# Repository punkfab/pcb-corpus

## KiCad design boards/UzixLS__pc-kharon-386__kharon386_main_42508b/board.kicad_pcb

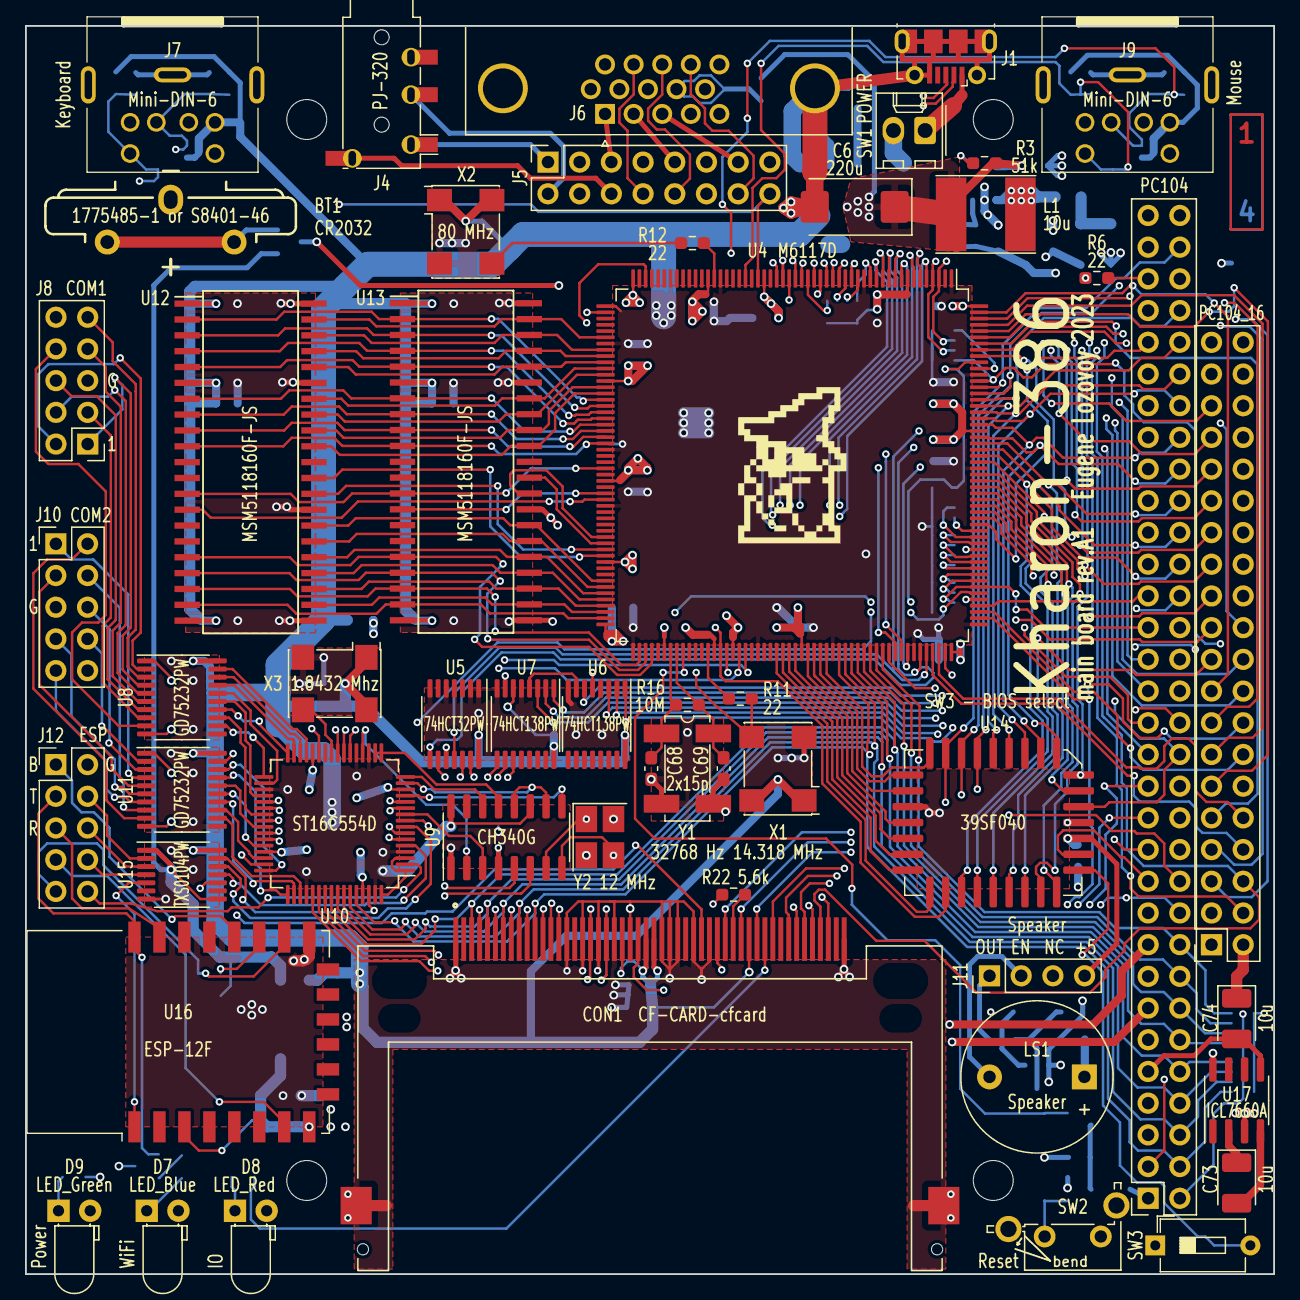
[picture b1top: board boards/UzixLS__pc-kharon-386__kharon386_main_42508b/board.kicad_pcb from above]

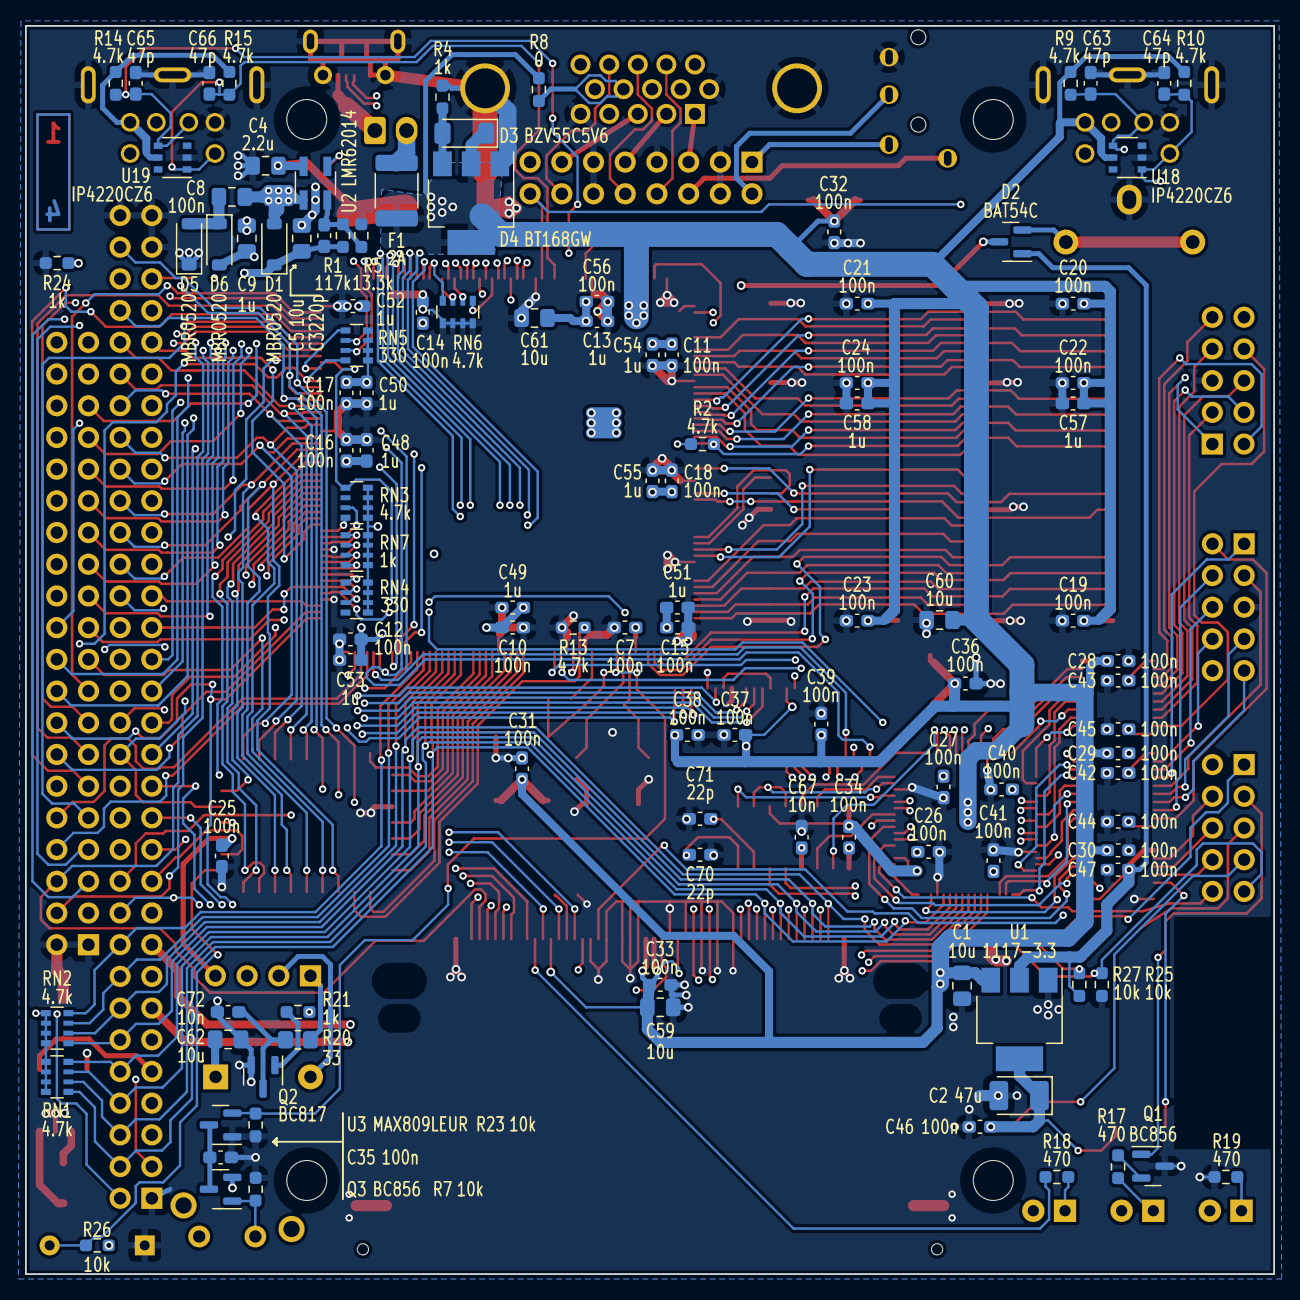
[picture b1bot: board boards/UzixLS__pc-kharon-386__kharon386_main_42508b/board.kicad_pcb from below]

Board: 4 copper layers, 100.0 x 100.0 mm, 169 parts (112 on the bottom side), 252 nets.

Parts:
BT1: 1775485-1 or S8401-46; CR2032V
C1, C5, C59, C60, C61, C62: 10u; C_0805_2012Metric_Pad1.18x1.45mm_HandSolder
C2: 47u; CP_EIA-3528-21_Kemet-B_Pad1.50x2.35mm_HandSolder
C3: 220p; C_0603_1608Metric_Pad1.08x0.95mm_HandSolder
C4: 2.2u; C_0805_2012Metric_Pad1.18x1.45mm_HandSolder
C6: 220u; CP_EIA-7343-31_Kemet-D_Pad2.25x2.55mm_HandSolder
C7, C10, C11, C12, C13, C14, C15, C16, C17, C18, C19, C20, C21, C22, C23, C24, C25, C26, C27, C28, C29, C30, C31, C32, C33, C34, C35, C36, C37, C38, C39, C40, C41, C42, C43, C44, C45, C46, C47: 100n; C_0603_1608Metric_Pad1.08x0.95mm_HandSolder
C8: 100n; C_0805_2012Metric_Pad1.18x1.45mm_HandSolder
C9: 1u; C_0805_2012Metric_Pad1.18x1.45mm_HandSolder
C48, C49, C50, C51, C52, C53, C54, C55, C56, C57, C58: 1u; C_0603_1608Metric_Pad1.08x0.95mm_HandSolder
C63, C64, C65, C66: 47p; C_0603_1608Metric_Pad1.08x0.95mm_HandSolder
C67, C72: 10n; C_0603_1608Metric_Pad1.08x0.95mm_HandSolder
C68, C69: 15p; C_0603_1608Metric_Pad1.08x0.95mm_HandSolder
C70, C71: 22p; C_0603_1608Metric_Pad1.08x0.95mm_HandSolder
C73, C74: 10u; CP_EIA-3528-21_Kemet-B_Pad1.50x2.35mm_HandSolder
CON1: CF-CARD-cfcard; TE_1734451-1-LONG
D1, D5, D6: MBR0520; D_SOD-123
D2: BAT54C; SOT-23
D3: BZV55C5V6; D_MiniMELF
D4: BT168GW; SOT-223-3_TabPin2
D7: LED_Blue; LED_D3.0mm_Horizontal_O1.27mm_Z6.0mm
D8: LED_Red; LED_D3.0mm_Horizontal_O1.27mm_Z6.0mm
D9: LED_Green; LED_D3.0mm_Horizontal_O1.27mm_Z6.0mm
F1: 2A; Fuse_1812_4532Metric_Pad1.30x3.40mm_HandSolder
H1, H2, H3, H4: Screw M3 dk=5mm L=4mm; MountingHole_3.2mm_M3_dk5.2mm_Mask
J1: USB_B_Micro; USB_Micro-B_Molex-105017-0001
J2: PC104_16; PinSocket_2x20_P2.54mm_Vertical
J3: PC104; PinSocket_2x32_P2.54mm_Vertical
J4: PJ-320; PJ-320A_D
J5: Conn_02x08_Odd_Even; PinSocket_2x08_P2.54mm_Vertical
J6: DB15_Female_HighDensity_MountingHoles; DSUB-15-HD_Female_Horizontal_P2.29x1.98mm_EdgePinOffset3.03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
J7, J9: Mini-DIN-6; minidin-6
J8: COM1; PinHeader_2x05_P2.54mm_Vertical
J10: COM2; PinHeader_2x05_P2.54mm_Vertical
J11: Conn_01x04; PinHeader_1x04_P2.54mm_Vertical
J12: ESP; PinHeader_2x05_P2.54mm_Vertical
L1: 10u; L_Taiyo-Yuden_NR-60xx_HandSoldering
LOGO1: graphic; black-mage-12.5x8.6
LS1: Speaker; Buzzer_12x9.5RM7.6
Q1, Q3: BC856; SOT-23
Q2: BC817; SOT-23
R1: 117k; R_0603_1608Metric_Pad0.98x0.95mm_HandSolder
R2, R9, R10, R13, R14, R15: 4.7k; R_0603_1608Metric_Pad0.98x0.95mm_HandSolder
R3: 51k; R_0603_1608Metric_Pad0.98x0.95mm_HandSolder
R4, R21, R24: 1k; R_0603_1608Metric_Pad0.98x0.95mm_HandSolder
R5: 13.3k; R_0603_1608Metric_Pad0.98x0.95mm_HandSolder
R6, R11, R12: 22; R_0603_1608Metric_Pad0.98x0.95mm_HandSolder
R7, R23, R25, R26, R27: 10k; R_0603_1608Metric_Pad0.98x0.95mm_HandSolder
R8: 0; R_0603_1608Metric_Pad0.98x0.95mm_HandSolder
R16: 10M; R_0603_1608Metric_Pad0.98x0.95mm_HandSolder
R17, R18, R19: 470; R_0603_1608Metric_Pad0.98x0.95mm_HandSolder
R20: 33; R_0805_2012Metric_Pad1.20x1.40mm_HandSolder
R22: 5.6k; R_0603_1608Metric_Pad0.98x0.95mm_HandSolder
RN1, RN2, RN3, RN6: 4.7k; R_Array_Convex_4x0603
RN4, RN5: 330; R_Array_Convex_4x0603
RN7: 1k; R_Array_Convex_4x0603
SW1: Jumper / Pin header 1x2 Pitch=2.54mm; Molex_KK-254_AE-6410-02A_1x02_P2.54mm_Vertical
SW2: SW_Push; SW_Tactile_SPST_Angled_PTS645Vx83-2LFS
SW3: SW_DIP_x01; SW_DIP_SPSTx01_Slide_6.7x4.1mm_W7.62mm_P2.54mm_LowProfile
U1: 1117-3.3; SOT-223-3_TabPin2
U2: LMR62014; SOT-23-5_HandSoldering
U3: MAX809LEUR; SOT-23
U4: M6117D; PQFP-208_28x28mm_P0.5mm
U5: 74HCT32PW; TSSOP-14_4.4x5mm_P0.65mm
U6, U7: 74HCT138PW; TSSOP-16_4.4x5mm_P0.65mm
U8, U11: GD75232PW; TSSOP-20_4.4x6.5mm_P0.65mm
U9: CH340G; SOIC-16_3.9x9.9mm_P1.27mm
U10: ST16C554D; LQFP-64_10x10mm_P0.5mm
U12, U13: MSM5118160F-JS; SOJ-42
U14: 39SF040; PLCC-32_11.4x14.0mm_P1.27mm-longpads
U15: TXS0104PW; TSSOP-14_4.4x5mm_P0.65mm
U16: ESP-12F; ESP-12E
U17: ICL7660A; SOIC-8_3.9x4.9mm_P1.27mm
U18, U19: IP4220CZ6; TSOP-6_1.65x3.05mm_P0.95mm
X1: 14.318 MHz; Oscillator_SMD_7050_7.0x5.0mm
X2: 80 MHz; Oscillator_SMD_7050_7.0x5.0mm
X3: 1.8432 Mhz; Oscillator_SMD_7050_7.0x5.0mm
Y1: 32768 Hz; Crystal_SMD_SeikoEpson_MC306-4Pin_8.0x3.2mm_HandSoldering
Y2: 12 MHz; Crystal_SMD_SeikoEpson_TSX3225-4Pin_3.2x2.5mm_HandSoldering

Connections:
+3V3: C2.1, C46.2, C47.2, D2.1, R27.2, U1.2 (VO), U15.1 (VCCA), U15.8 (OE), U16.3 (EN), U16.8 (VCC)
+5V: C1.2, C4.2, C6.1, C10.2, C11.2, C12.2, C13.2, C14.2, C15.2, C16.2, C17.2, C18.2, C19.2, C20.2, C21.2, C22.2, C23.2, C24.2, C25.2, C26.2, C27.2, C28.2, C29.2, C30.2, C31.2, C32.2, C33.2, C34.1, C36.1, C37.1, C38.1, C39.1, C40.1, C41.1, C48.2, C49.2, C50.2, C51.2, C52.2, C53.2, C54.1, C55.1, C56.1, C57.1, C58.1, C59.1, C60.1, C61.1, C62.1, CON1.13 (VCC2), CON1.36 (~WE), CON1.38 (VCC1), CON1.44 (~REG), D3.1 (K), D4.2 (A), D7.2 (A), D8.2 (A), D9.2 (A), F1.1, J2.34, J3.5, J3.57, J7.4, J9.4, J11.4, L1.1, LS1.1, Q3.2 (E), R2.1, R3.1, R8.1, R9.1, R10.1, R14.1, R15.1, R26.2, RN1.5 (R4.2), RN1.6 (R3.2), RN1.7 (R2.2), RN1.8 (R1.2), RN2.5 (R4.2), RN2.6 (R3.2), RN2.7 (R2.2), RN2.8 (R1.2), RN3.5 (R4.2), RN3.6 (R3.2), RN3.7 (R2.2), RN3.8 (R1.2), RN4.5 (R4.2), RN4.6 (R3.2), RN4.7 (R2.2), RN4.8 (R1.2), RN5.5 (R4.2), RN5.6 (R3.2), RN5.7 (R2.2), RN5.8 (R1.2), RN7.5 (R4.2), RN7.6 (R3.2), RN7.7 (R2.2), RN7.8 (R1.2), SW2.1, U1.3 (VI), U2.5 (Vin), U4.1 (VCC1), U4.15 (VCC2), U4.38 (VCC3), U4.46 (VCC4), U4.53 (VCC5), U4.59 (VCC6), U4.76 (VCC7), U4.85 (VCC8), U4.105 (VCC9), U4.125 (VCC11), U4.137 (VCC12), U4.150 (VCC13), U4.157 (VCC14), U4.182 (VCC15), U4.197 (VCC16), U5.14 (VCC), U6.16 (VCC), U7.6 (E3), U7.16 (VCC), U8.20 (V_{CC}), U9.11 (~RI), U9.16 (VCC), U10.4 (VCC), U10.19 (RIB#), U10.21 (VCC)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
+12V: C3.1, C5.2, C42.2, C43.2, D1.1 (K), J3.17, R1.1, R24.2, U8.1 (V_{DD}), U11.1 (V_{DD})
+BATT: C7.1, D2.3, U4.110 (VBAT)
-5V: C74.2, J3.9, U17.5 (VOUT)
-12V: C9.1, C44.2, C45.2, D6.2 (A), J3.13, U8.10 (V_{SS}), U11.10 (V_{SS})
/0x2E8: U7.11 (O4), U10.7 (CSA#)
/0x2F8: U7.9 (O6), U10.42 (CSD#)
/0x3E8: U7.10 (O5), U10.11 (CSB#)
/0x3F8: U7.7 (O7), U10.38 (CSC#)
/14MHz: R6.2, R11.2, X1.3 (OUT)
/AEN: J3.22, RN3.1 (R1.1), U4.199 (AEN), U6.5 (E2)
/BALE: J3.55, U4.173 (BALE)
/BD0: R2.2, U4.75 (BD0), U12.10 (DQ7), U13.10 (DQ7)
/BD1: U4.74 (BD1), U12.9 (DQ6), U13.9 (DQ6)
/BD2: U4.73 (BD2), U12.8 (DQ5), U13.8 (DQ5)
/BD3: U4.72 (BD3), U12.7 (DQ4), U13.7 (DQ4)
/BD4: U4.71 (BD4), U12.5 (DQ3), U13.5 (DQ3)
/BD5: U4.70 (BD5), U12.4 (DQ2), U13.4 (DQ2)
/BD6: U4.69 (BD6), U12.3 (DQ1), U13.3 (DQ1)
/BD7: U4.68 (BD7), U12.2 (DQ0), U13.2 (DQ0)
/BD8: U4.67 (BD8), U12.33 (DQ8), U13.33 (DQ8)
/BD9: U4.66 (BD9), U12.34 (DQ9), U13.34 (DQ9)
/BD10: U4.64 (BD10), U12.35 (DQ10), U13.35 (DQ10)
/BD11: U4.63 (BD11), U12.36 (DQ11), U13.36 (DQ11)
/BD12: U4.62 (BD12), U12.38 (DQ12), U13.38 (DQ12)
/BD13: U4.61 (BD13), U12.39 (DQ13), U13.39 (DQ13)
/BD14: U4.60 (BD14), U12.40 (DQ14), U13.40 (DQ14)
/BD15: U4.58 (BD15), U12.41 (DQ15), U13.41 (DQ15)
/CAS0J0: U4.93 (CAS0LJ), U12.31 (~LCAS)
/CAS0J1: U4.92 (CAS0HJ), U12.30 (~UCAS)
/CAS1J0: U4.91 (CAS1LJ), U13.31 (~LCAS)
/CAS1J1: U4.90 (CAS1HJ), U13.30 (~UCAS)
/CD_COM1: U8.17 (RY3), U10.31 (CDC#)
/CD_COM2: U10.49 (CDD#), U11.17 (RY3)
/CLK2: R12.2, X2.3 (OUT)
/CTS1: J8.8, U8.9 (RA5)
/CTS2: J10.8, U11.2 (RA1)
/CTS_COM1: U8.12 (RY5), U10.33 (CTSC#)
/CTS_COM2: U10.47 (CTSD#), U11.19 (RY1)
/CTS_ESP: J12.10, U10.2 (CTSA#)
/CTS_USB: U9.14 (~RTS), U10.16 (CTSB#)
/DACK0: J2.18, RN6.7 (R2.2), U4.16 (DACK0J)
/DACK1: J3.33, RN6.6 (R3.2), U4.18 (DACK1J)
/DACK2: J3.51, U4.20 (DACK2J)
/DACK3: J3.29, U4.22 (DACK3J)
/DACK5: J2.22, RN6.5 (R4.2), U4.24 (DACK5J)
/DACK6: J2.26, U4.26 (DACK6J)
/DACK7: J2.30, U4.28 (DACK7J)
/DCD1: J8.1, U8.4 (RA3)
/DCD2: J10.1, U11.4 (RA3)
/DRQ0: J2.20, U4.17 (DRQ0)
/DRQ1: J3.35, U4.19 (DRQ1)
/DRQ2: J3.11, U4.21 (DRQ2)
/DRQ3: J3.31, U4.23 (DRQ3)
/DRQ5: J2.24, U4.25 (DRQ5)
/DRQ6: J2.28, U4.27 (DRQ6)
/DRQ7: J2.32, U4.29 (DRQ7)
/DSR1: J8.6, U8.7 (RA4)
/DSR2: J10.6, U11.3 (RA2)
/DSR_COM1: U8.14 (RY4), U10.32 (DSRC#)
/DSR_COM2: U10.48 (DSRD#), U11.18 (RY2)
/DSR_USB: U9.13 (~DTR), U10.17 (DSRB#), U10.18 (CDB#)
/DTR1: J8.4, U8.5 (DY1)
/DTR2: J10.4, U11.8 (DY3)
/DTR_COM1: U8.16 (DA1), U10.34 (DTRC#)
/DTR_COM2: U10.46 (DTRD#), U11.13 (DA3)
/DTR_USB: U9.10 (~DSR), U9.12 (~DCD), U10.15 (DTRB#)
/ESP_BOOT: J12.1, U16.18 (GPIO0)
/ESP_CTS: J12.7, U16.7 (GPIO13)
/ESP_RST: U15.5 (A4), U16.1 (~RST)
/ESP_RTS: J12.9, R25.1, U16.16 (GPIO15)
/ESP_RX: J12.5, U16.21 (GPIO3/RXD)
/ESP_TX: J12.3, Q1.1 (B), U16.22 (GPIO1/TXD)
/HDCS0: CON1.7 (~CS0), U4.50 (HDCS0J)
/HDCS1: CON1.32 (~CS1), U4.54 (HDCS1J)
/IOCHK: J3.2, RN5.4 (R4.1), U4.196 (IOCHKJ)
/IOCHRDY: CON1.42 (IORDY), J3.20, RN4.2 (R2.1), U4.164 (IOCHRDY)
/IOCS16: CON1.24 (~IOCS16), J2.6, RN5.2 (R2.1), U4.3 (IO16J)
/IOR: CON1.34 (~IORD), J3.27, RN7.4 (R4.1), U4.166 (IORJ), U10.40 (IOR#)
/IOW: CON1.35 (~IOWR), J3.25, RN7.3 (R3.1), U4.167 (IOWJ), U10.9 (IOW#)
/IRQ3: J3.49, U4.152 (IRQ3), U5.11
/IRQ4: J3.47, U4.151 (IRQ4), U5.8
/IRQ5: J3.45, U4.149 (IRQ5)
/IRQ6: J3.43, U4.148 (IRQ6)
/IRQ7: J3.41, U4.147 (IRQ7)
/IRQ9: J3.7, U4.146 (IRQ9)
/IRQ10: J2.8, U4.153 (IRQ10)
/IRQ11: J2.10, U4.154 (IRQ11)
/IRQ14: CON1.37 (INTRQ), J2.16, U4.158 (IRQ14)
/IRQ15: J2.14, U4.159 (IRQ15)
/KBCLK: C64.1, J7.5, R10.2, U4.122 (KBCLK), U18.1
/KBDAT: C63.1, J7.1, R9.2, U4.123 (KBDATA), U18.4
/KBSJ: R13.2, U4.119 (ROMKBCSJ), U14.22 (~CE)
/LA17: J2.17, U4.207 (LA17)
/LA18: J2.15, U4.206 (LA18)
/LA19: J2.13, U4.205 (LA19)
/LA20: J2.11, U4.204 (LA20)
/LA21: J2.9, U4.203 (LA21)
/LA22: J2.7, U4.202 (LA22)
/LA23: J2.5, U4.201 (LA23)
/MA0: U4.108 (MA0), U12.17 (MA0), U13.17 (MA0)
/MA1: U4.107 (MA1), U12.18 (MA1), U13.18 (MA1)
/MA2: U4.106 (MA2), U12.19 (MA2), U13.19 (MA2)
/MA3: U4.103 (MA3), U12.20 (MA3), U13.20 (MA3)
/MA4: U4.102 (MA4), U12.23 (MA4), U13.23 (MA4)
/MA5: U4.101 (MA5), U12.24 (MA5), U13.24 (MA5)
/MA6: U4.100 (MA6), U12.25 (MA6), U13.25 (MA6)
/MA7: U4.99 (MA7), U12.26 (MA7), U13.26 (MA7)
/MA8: U4.98 (MA8), U12.27 (MA8), U13.27 (MA8)
/MA9: U4.97 (MA9), U12.28 (MA9), U13.28 (MA9)
/MASTER: J2.36, RN5.1 (R1.1), U4.198 (MASTERJ)
/MEMCS16: J2.4, RN5.3 (R3.1), U4.4 (MEM16J)
/MEMR: J2.19, RN3.3 (R3.1), U4.171 (MRDJ), U14.24 (~OE)
/MEMW: J2.21, RN3.4 (R4.1), U4.172 (MWTJ)
/MSCLK: C66.1, J9.5, R15.2, U4.34 (MSCLK), U19.1
/MSDAT: C65.1, J9.1, R14.2, U4.155 (IRQ12/MSDATA), U19.4
/NOWS: J3.15, RN4.1 (R1.1), U4.165 (NOWSJ)
/PWG: R23.1, U3.2 (~RST), U4.113 (PWG)
/RASJ0: U4.84 (RAS0J), U12.14 (~RAS)
/RASJ1: U4.83 (RAS1J), U13.14 (~RAS)
/REFRESH: J3.37, RN4.3 (R3.1), U4.163 (REFRESHJ)
/RESETL: CON1.41 (~RESET), U4.120 (RESETLJ), U15.10 (B4)
/RI1: J8.9, U8.3 (RA2)
/RI2: J10.9, U11.7 (RA4)
/RI_COM1: U8.18 (RY2), U10.30 (RIC#)
/RI_COM2: U10.50 (RID#), U11.14 (RY4)
/RSTDRV: J3.3, U4.162 (RSTDRV), U10.27 (RESET)
/RTS1: J8.7, U8.6 (DY2)
/RTS2: J10.7, U11.6 (DY2)
/RTS_COM1: U8.15 (DA2), U10.36 (RTSC#)
/RTS_COM2: U10.44 (RTSD#), U11.15 (DA2)
/RTS_ESP: U10.5 (RTSA#), U15.11 (B3)
/RTS_USB: U9.9 (~CTS), U10.13 (RTSB#)
/RX1: J8.2, U8.2 (RA1)
/RX2: J10.2, U11.9 (RA5)
/RX_COM1: U8.19 (RY1), U10.29 (RXC)
/RX_COM2: U10.51 (RXD), U11.12 (RY5)
/RX_ESP: U10.62 (RXA), U15.13 (B1)
/RX_USB: U9.2 (TXD), U10.20 (RXB)
/SA0: CON1.20 (A0), J3.62, U4.195 (SA0), U10.24 (A0), U14.12 (A0)
/SA1: CON1.19 (A1), J3.60, U4.194 (SA1), U10.23 (A1), U14.11 (A1)
/SA2: CON1.18 (A2), J3.58, U4.193 (SA2), U10.22 (A2), U14.10 (A2)
/SA3: J3.56, U4.192 (SA3), U7.3 (A2), U14.9 (A3)
/SA4: J3.54, U4.191 (SA4), U7.2 (A1), U14.8 (A4)
/SA5: J3.52, U4.190 (SA5), U6.6 (E3), U14.7 (A5)
/SA6: J3.50, U4.189 (SA6), U6.1 (A0), U14.6 (A6)
/SA7: J3.48, U4.187 (SA7), U6.2 (A1), U14.5 (A7)
/SA8: J3.46, U4.186 (SA8), U7.1 (A0), U14.27 (A8)
/SA9: J3.44, U4.185 (SA9), U6.3 (A2), U14.26 (A9)
/SA10: J3.42, U4.184 (SA10), U14.23 (A10)
/SA11: J3.40, U4.183 (SA11), U14.25 (A11)
/SA12: J3.38, U4.181 (SA12), U14.4 (A12)
/SA13: J3.36, U4.180 (SA13), U14.28 (A13)
/SA14: J3.34, U4.179 (SA14), U14.29 (A14)
/SA15: J3.32, U4.178 (SA15), U14.3 (A15)
/SA16: J3.30, U4.177 (SA16), U14.2 (A16)
/SA17: J3.28, U4.176 (SA17)
/SA18: J3.26, U4.175 (SA18)
/SA19: J3.24, U4.174 (SA19)
/SBHE: J2.3, U4.200 (BHEJ)
/SD0: CON1.21 (D0), J3.18, RN2.4 (R4.1), U4.145 (SD0), U10.53 (D0)
/SD1: CON1.22 (D1), J3.16, RN2.3 (R3.1), U4.144 (SD1), U10.54 (D1)
/SD2: CON1.23 (D2), J3.14, RN2.2 (R2.1), U4.143 (SD2), U10.55 (D2)
/SD3: CON1.2 (D3), J3.12, RN2.1 (R1.1), U4.142 (SD3), U10.56 (D3)
/SD4: CON1.3 (D4), J3.10, RN1.4 (R4.1), U4.141 (SD4), U10.57 (D4)
/SD5: CON1.4 (D5), J3.8, RN1.3 (R3.1), U4.140 (SD5), U10.58 (D5)
/SD6: CON1.5 (D6), J3.6, RN1.2 (R2.1), U4.139 (SD6), U10.59 (D6)
/SD7: CON1.6 (D7), J3.4, RN1.1 (R1.1), U4.138 (SD7), U10.60 (D7)
/SD8: CON1.47 (D8), J2.23, U4.5 (SD8)
/SD9: CON1.48 (D9), J2.25, U4.6 (SD9)
/SD10: CON1.49 (D10), J2.27, U4.7 (SD10)
/SD11: CON1.27 (D11), J2.29, U4.9 (SD11)
/SD12: CON1.28 (D12), J2.31, U4.10 (SD12)
/SD13: CON1.29 (D13), J2.33, U4.11 (SD13)
/SD14: CON1.30 (D14), J2.35, U4.12 (SD14)
/SD15: CON1.31 (D15), J2.37, U4.13 (SD15)
/SMEMR: J3.23, RN7.2 (R2.1), U4.168 (SMEMRJ)
/SMEMW: J3.21, RN7.1 (R1.1), U4.170 (SMEMWJ), U14.31 (~WE)
/SND_L: J4.T, J5.1
/SND_R: J4.R1, J5.2
/SPKR: J5.16, R21.1, U4.32 (SPKR)
/SYSCLK: J3.39, U4.160 (ATCLK)
/TC: J3.53, RN6.8 (R1.2), U4.14 (TC)
/TX1: J8.3, U8.8 (DY3)
/TX2: J10.3, U11.5 (DY1)
/TX_COM1: U8.13 (DA3), U10.39 (TXC)
/TX_COM2: U10.41 (TXD), U11.16 (DA1)
/TX_ESP: U10.8 (TXA), U15.12 (B2)
/TX_USB: U9.3 (RXD), U10.10 (TXB)
/UART_INTA: U5.12, U10.6 (INTA)
/UART_INTB: U5.9, U10.12 (INTB)
/UART_INTC: U5.10, U10.37 (INTC)
/UART_INTD: U5.13, U10.43 (INTD)
/USB_DN: J1.2 (D-), U9.6 (UD-)
/USB_DP: J1.3 (D+), U9.5 (UD+)
/VGA_B: J5.13, J6.3
/VGA_G: J5.9, J6.2
/VGA_HS: J5.10, J6.13
/VGA_MON: J5.8, J6.12
/VGA_R: J5.5, J6.1
/VGA_VS: J5.14, J6.14
/WEJ: U4.79 (WEJ), U12.13 (~W), U13.13 (~W)
/XD0: U4.136 (XD0), U14.13 (D0)
/XD1: U4.135 (XD1), U14.14 (D1)
/XD2: U4.134 (XD2), U14.15 (D2)
/XD3: U4.133 (XD3), U14.17 (D3)
/XD4: U4.131 (XD4), U14.18 (D4)
/XD5: U4.130 (XD5), U14.19 (D5)
/XD6: U4.129 (XD6), U14.20 (D6)
/XD7: U4.128 (XD7), U14.21 (D7)
/~CF_BUSY: CON1.45 (~DASP), R18.2
GND: BT1.2 (-), C1.1, C2.2, C4.1, C5.1, C6.2, C7.2, C9.2, C10.1, C11.1, C12.1, C13.1, C14.1, C15.1, C16.1, C17.1, C18.1, C19.1, C20.1, C21.1, C22.1, C23.1, C24.1, C25.1, C26.1, C27.1, C28.1, C29.1, C30.1, C31.1, C32.1, C33.1, C34.2, C35.2, C36.2, C37.2, C38.2, C39.2, C40.2, C41.2, C42.1, C43.1, C44.1, C45.1, C46.1, C47.1, C48.1, C49.1, C50.1, C51.1, C52.1, C53.1, C54.2, C55.2, C56.2, C57.2, C58.2, C59.2, C60.2, C61.2, C62.2, C63.2, C64.2, C65.2, C66.2, C67.1, C68.2, C69.2, C70.2, C71.2, C72.2, C74.1, CON1.1 (GND1), CON1.8 (A10), CON1.9 (~ATASEL), CON1.10 (A9), CON1.11 (A8), CON1.12 (A7), CON1.14 (A6), CON1.15 (A5), CON1.16 (A4), CON1.17 (A3), CON1.39 (~CSEL), CON1.50 (GND2), CON1.S1 (Shield), CON1.S2 (Shield), D4.1 (K), D5.1 (K), J1.5 (GND), J1.6 (Shield), J2.1, J2.2, J2.38, J2.40, J3.1, J3.61, J3.63, J3.64, J4.R2, J5.3, J5.4, J5.7, J5.11, J5.12, J6.0, J6.5, J6.6, J6.7, J6.8, J6.10, J7.0, J7.3, J8.5, J9.0, J9.3, J10.5, J12.2, Q1.3 (C), Q2.2 (E), R4.2, R5.1, R7.2, R13.1, R19.2, R22.2, R23.2, R24.1, R25.2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
unnamed: BT1.1 (+), D2.2
unnamed: CON1.43 (~INPACK), R22.1
unnamed: C8.1, D1.2 (A), L1.2, U2.1 (SW)
unnamed: D3.2 (A), D4.3 (G), R4.1
unnamed: C8.2, D5.2 (A), D6.1 (K)
unnamed: D7.1 (K), R17.1
unnamed: D8.1 (K), R18.1
unnamed: D9.1 (K), R19.1
unnamed: J1.1 (VBUS), SW1.1 (A)
unnamed: J3.59, R6.1
unnamed: J4.S, J5.6
unnamed: J6.9, R8.2
unnamed: J11.1, R20.1
unnamed: J11.2, LS1.2
unnamed: J12.4, U15.2 (A1)
unnamed: J12.6, U15.3 (A2)
unnamed: J12.8, U15.4 (A3)
unnamed: Q1.2 (E), R17.2
unnamed: Q2.1 (B), R21.2
unnamed: C72.1, Q2.3 (C), R20.2
unnamed: Q3.1 (B), R7.1, SW2.2
unnamed: C35.1, Q3.3 (C), U3.3 (VCC)
unnamed: F1.2, SW1.2 (B)
unnamed: C3.2, R1.2, R5.2, U2.3 (FB)
unnamed: R3.2, U2.4 (~SHDN)
unnamed: R12.1, U4.39 (BCLK2)
unnamed: R11.1, U4.117 (OSC14M)
unnamed: C68.1, R16.1, U4.111 (XTAL1), Y1.1
unnamed: C69.1, R16.2, U4.112 (XTAL2), Y1.4
unnamed: U6.7 (O7), U7.4 (E1)
unnamed: C67.2, U9.4 (V3)
unnamed: C71.1, U9.7 (XI), Y2.1
unnamed: C70.1, U9.8 (XO), Y2.3
unnamed: U10.1 (DSRA#), U10.3 (DTRA#), U10.64 (CDA#)
unnamed: U10.25 (XTAL1), X3.3 (OUT)
unnamed: R26.1, SW3.2, U14.30 (A17)
unnamed: R27.1, U16.17 (GPIO2)
unnamed: C73.1, U17.2 (CAP+)
unnamed: C73.2, U17.4 (CAP-)

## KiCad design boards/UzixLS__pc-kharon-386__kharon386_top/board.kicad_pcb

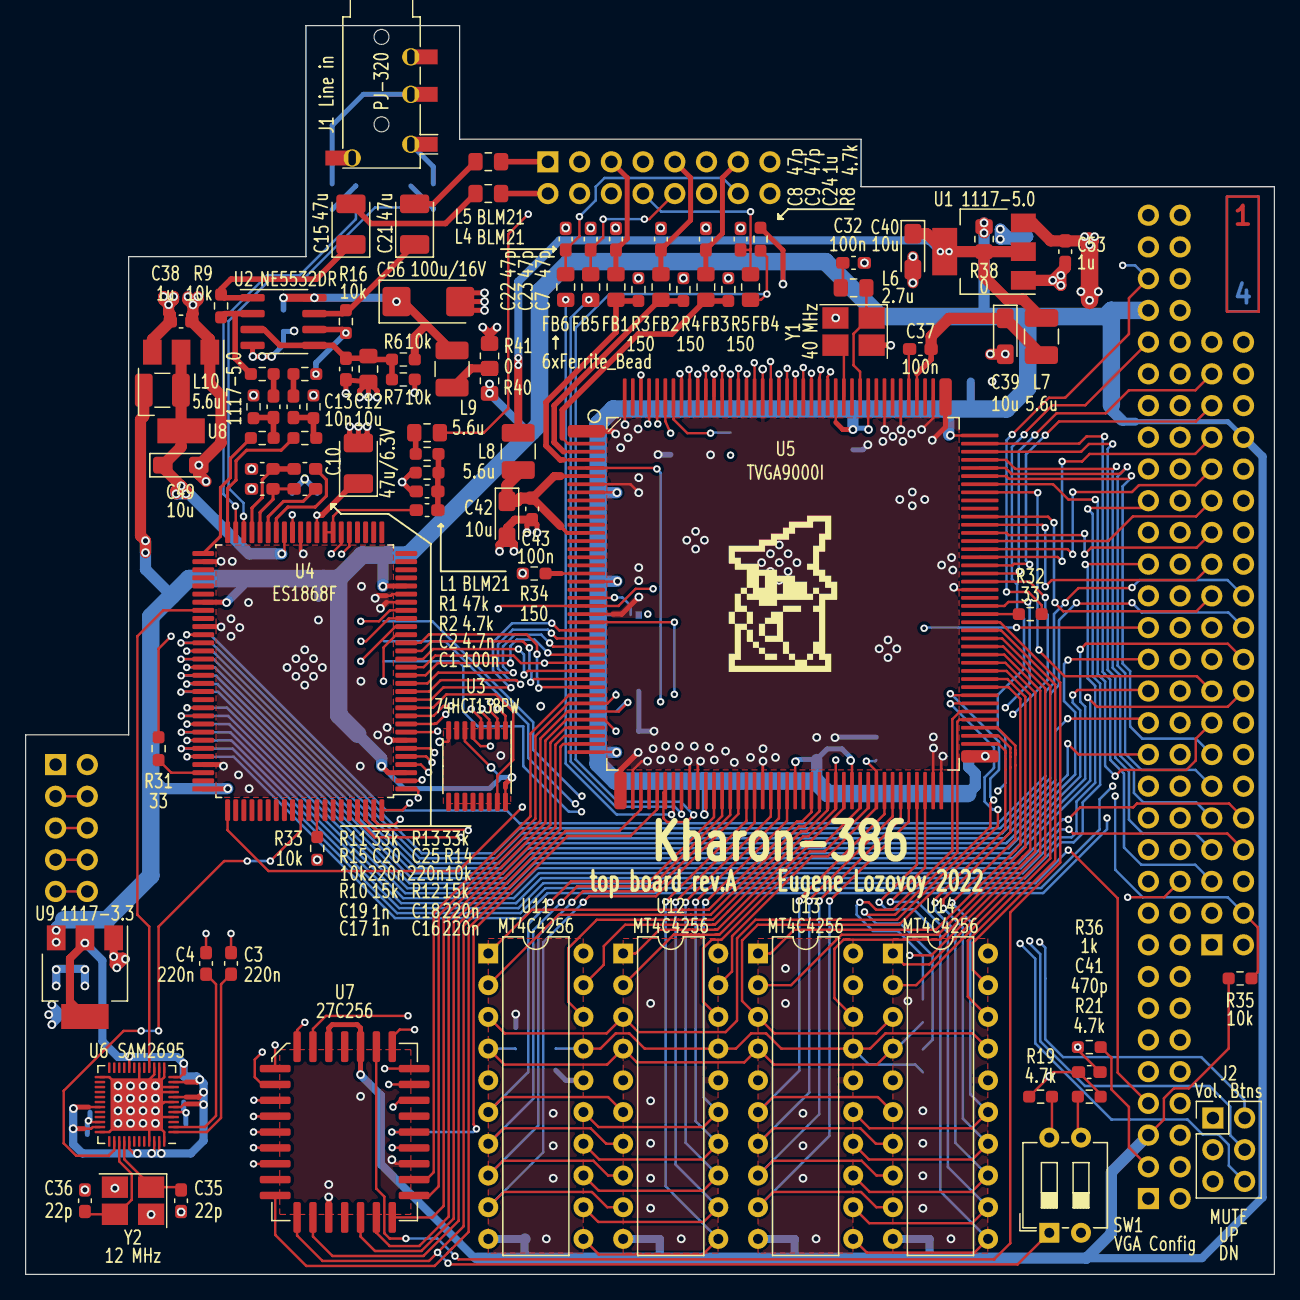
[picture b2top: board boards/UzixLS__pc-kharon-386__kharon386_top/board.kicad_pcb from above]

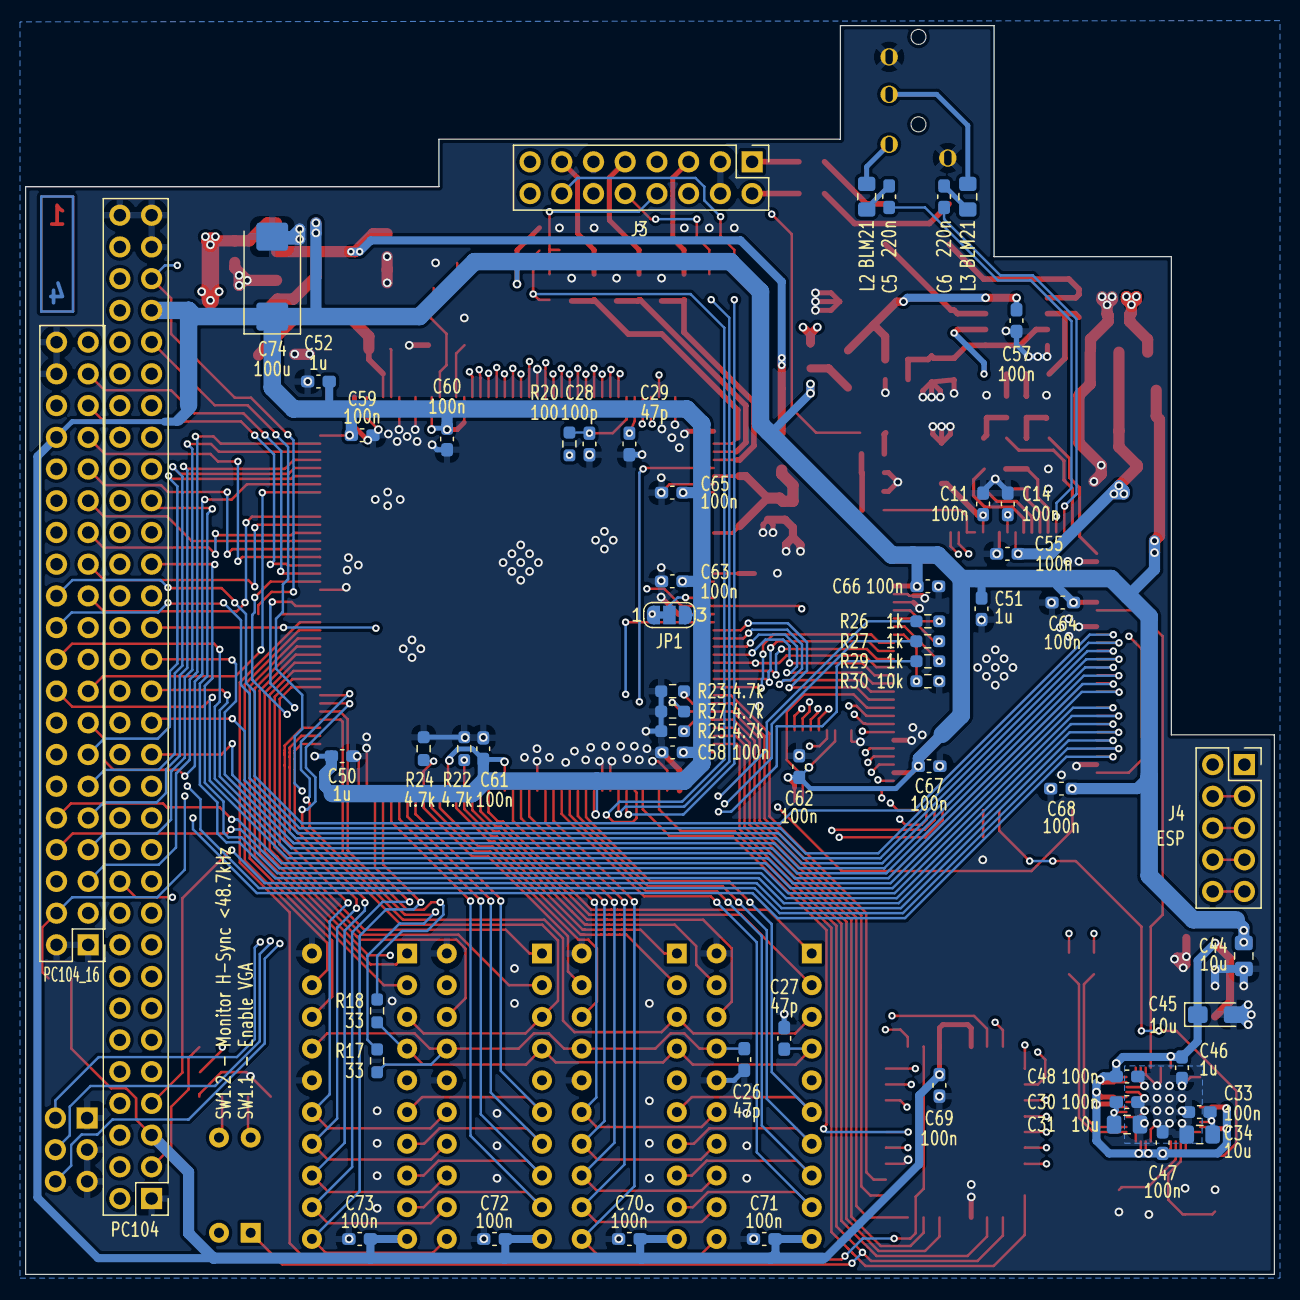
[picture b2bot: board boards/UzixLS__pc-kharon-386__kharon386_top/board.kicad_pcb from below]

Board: 4 copper layers, 100.0 x 100.0 mm, 152 parts (58 on the bottom side), 204 nets.

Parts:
C1, C11, C14, C30, C32, C33, C37, C43, C47, C48, C55, C57, C58, C59, C60, C61, C62, C63, C64, C65, C66, C67, C68, C69, C70, C71, C72, C73: 100n; C_0603_1608Metric_Pad1.08x0.95mm_HandSolder
C2: 4.7n; C_0603_1608Metric_Pad1.08x0.95mm_HandSolder
C3, C4, C5, C6, C16, C18, C20, C25: 220n; C_0603_1608Metric_Pad1.08x0.95mm_HandSolder
C7, C8, C9, C22, C23, C26, C27, C29: 47p; C_0603_1608Metric_Pad1.08x0.95mm_HandSolder
C10: 47u/6.3V; CP_EIA-3528-21_Kemet-B_Pad1.50x2.35mm_HandSolder
C12, C31, C34, C44: 10u; C_0805_2012Metric_Pad1.18x1.45mm_HandSolder
C13: 10n; C_0603_1608Metric_Pad1.08x0.95mm_HandSolder
C15, C21: 47u; CP_EIA-3528-21_Kemet-B_Pad1.50x2.35mm_HandSolder
C17, C19: 1n; C_0603_1608Metric_Pad1.08x0.95mm_HandSolder
C24, C38, C46, C50, C51, C52, C53: 1u; C_0603_1608Metric_Pad1.08x0.95mm_HandSolder
C28: 100p; C_0603_1608Metric_Pad1.08x0.95mm_HandSolder
C35, C36: 22p; C_0603_1608Metric_Pad1.08x0.95mm_HandSolder
C39, C40, C42, C45, C49: 10u; CP_EIA-3216-18_Kemet-A_Pad1.58x1.35mm_HandSolder
C41: 470p; C_0603_1608Metric_Pad1.08x0.95mm_HandSolder
C56: 100u/16V; CP_EIA-6032-28_Kemet-C_Pad2.25x2.35mm_HandSolder
C74: 100u; CP_EIA-7343-31_Kemet-D_Pad2.25x2.55mm_HandSolder
FB1, FB2, FB3, FB4, FB5, FB6: Ferrite_Bead; L_0805_2012Metric_Pad1.15x1.40mm_HandSolder
J1: PJ-320; PJ-320A_D
J2: Vol. Btns; PinHeader_2x03_P2.54mm_Vertical
J3: Conn_02x07_Odd_Even; PinHeader_2x08_P2.54mm_Vertical
J4: ESP; PinSocket_2x05_P2.54mm_Vertical
J5: PC104_16; PinHeader_2x20_P2.54mm_Vertical
J6: PC104; PinHeader_2x32_P2.54mm_Vertical
JP1: SolderJumper_3_Bridged12; SolderJumper-3_P1.3mm_Bridged12_RoundedPad1.0x1.5mm_NumberL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
L1, L2, L3, L4, L5: BLM21PG331BH1D; L_0805_2012Metric_Pad1.15x1.40mm_HandSolder
L6: 2.7u; L_0805_2012Metric_Pad1.15x1.40mm_HandSolder
L7, L8, L9, L10: 5.6u; L_1210_3225Metric_Pad1.42x2.65mm_HandSolder
LOGO1: graphic; black-mage-12.5x8.6
R1: 47k; R_0603_1608Metric_Pad0.98x0.95mm_HandSolder
R2, R8, R19, R21, R22, R23, R24, R25, R37: 4.7k; R_0603_1608Metric_Pad0.98x0.95mm_HandSolder
R3, R4, R5, R34: 150; R_0603_1608Metric_Pad0.98x0.95mm_HandSolder
R6, R7, R9, R14, R15, R16, R30, R33, R35: 10k; R_0603_1608Metric_Pad0.98x0.95mm_HandSolder
R10, R12: 15k; R_0603_1608Metric_Pad0.98x0.95mm_HandSolder
R11, R13: 33k; R_0603_1608Metric_Pad0.98x0.95mm_HandSolder
R17, R18, R31, R32: 33; R_0603_1608Metric_Pad0.98x0.95mm_HandSolder
R20: 100; R_0603_1608Metric_Pad0.98x0.95mm_HandSolder
R26, R27, R29, R36: 1k; R_0603_1608Metric_Pad0.98x0.95mm_HandSolder
R38, R40, R41: 0; R_0805_2012Metric_Pad1.20x1.40mm_HandSolder
SW1: VGA Config; SW_DIP_SPSTx02_Slide_6.7x6.64mm_W7.62mm_P2.54mm_LowProfile
U1, U8: 1117-5.0; SOT-223-3_TabPin2
U2: NE5532DR; SOIC-8_3.9x4.9mm_P1.27mm
U3: 74HCT138PW; TSSOP-16_4.4x5mm_P0.65mm
U4: ES1868F; PQFP-100_14x20mm_P0.65mm
U5: TVGA9000I; PQFP-160_28x28mm_P0.65mm_LongPads
U6: SAM2695; QFN-48-1EP_6x6mm_P0.4mm_EP4.2x4.2mm
U7: 27C256; PLCC-32_11.4x14.0mm_P1.27mm-longpads
U9: 1117-3.3; SOT-223-3_TabPin2
U11, U12, U13, U14: MT4C4256; DIP-20_W7.62mm
Y1: 40 MHz; Crystal_SMD_SeikoEpson_TSX3225-4Pin_3.2x2.5mm_HandSoldering
Y2: 12 MHz; Crystal_SMD_SeikoEpson_TSX3225-4Pin_3.2x2.5mm_HandSoldering

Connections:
+3V3: C45.1, C46.2, C47.2, C48.2, U6.6 (VA33), U6.8 (VD33), U6.11 (VD33), U6.12 (~WR), U6.20 (VD33), U6.31 (VD33), U6.35 (VD33), U6.41 (VD33), U6.46 (VD33), U6.47 (XDIV), U9.2 (VO)
+5V: C44.2, C50.1, C51.1, C52.1, C58.1, C59.1, C60.1, C61.1, C62.1, C63.1, C64.1, C65.1, C66.1, C67.1, C68.1, C69.1, C70.1, C71.1, C72.1, C73.1, C74.1, J5.34, J6.5, J6.57, JP1.3 (B), L10.1, R8.1, R35.1, R38.1, R40.1, U3.6 (E3), U3.16 (VCC), U4.3 (VCC), U4.26 (VCC), U4.57 (VCC), U4.80 (VCC), U5.8 (DVDD2), U5.19 (VDD), U5.40 (VDD), U5.51 (ESYNC), U5.62 (VDD), U5.69 (VDD), U5.81 (VDD), U5.120 (VDD), U5.130 (DVDD1), U5.134 (VDD), U7.2 (A15), U7.32 (VCC), U9.3 (VI), U11.10 (VCC), U12.10 (VCC), U13.10 (VCC), U14.10 (VCC)
+12V: C38.1, C53.1, J6.17, R41.1, U1.3 (VI), U8.3 (VI)
/A0: J6.62, U4.99 (A0), U5.135 (SA0)
/A1: J6.60, U4.100 (A1), U5.136 (SA1), U7.11 (A0)
/A2: J6.58, U4.1 (A2), U5.137 (SA2), U7.10 (A1)
/A3: J6.56, U4.2 (A3), U5.138 (SA3), U7.9 (A2)
/A4: J6.54, U4.4 (A4), U5.139 (SA4), U7.8 (A3)
/A5: J6.52, U4.5 (A5), U5.140 (SA5), U7.7 (A4)
/A6: J6.50, U4.6 (A6), U5.141 (SA6), U7.6 (A5)
/A7: J6.48, U4.8 (A7), U5.142 (SA7), U7.5 (A6)
/A8: J6.46, U4.9 (A8), U5.144 (SA8), U7.4 (A7)
/A9: J6.44, U4.10 (A9), U5.145 (SA9), U7.29 (A8)
/A10: J6.42, U4.97 (A10), U5.146 (SA10), U7.28 (A9)
/A11: J6.40, U4.98 (A11), U5.147 (SA11), U7.24 (A10)
/A12: J6.38, U3.4 (E1), U5.148 (SA12), U7.27 (A11)
/A13: J6.36, U3.3 (A2), U5.149 (SA13), U7.3 (A12)
/A14: J6.34, U3.2 (A1), U5.150 (SA14), U7.30 (A13)
/A15: J6.32, U3.1 (A0), U5.151 (SA15)
/A16: J6.30, U5.152 (SA16)
/AEN: J6.22, U3.5 (E2), U5.22 (AEN)
/ALE: J6.55, JP1.1 (A)
/AOUT_L: J3.1, L5.2
/AOUT_R: J3.2, L4.2
/AVDD1: C37.2, C39.1, L7.2, U5.124 (AVDD1)
/AVDD2: C42.1, C43.1, L8.2, U5.6 (AVDD2), U5.13 (AVDD2)
/AVDD_ES: C49.1, C55.1, L10.2, U4.43 (VDDA), U8.2 (VO)
/AVDD_OP: C56.1, C57.1, L9.2, R6.2, U2.8 (V+)
/B: FB3.1, R5.1, U5.2 (B)
/D0: J6.18, U4.12 (D0), U5.25 (SD0)
/D1: J6.16, U4.13 (D1), U5.26 (SD1)
/D2: J6.14, U4.14 (D2), U5.27 (SD2)
/D3: J6.12, U4.15 (D3), U5.28 (SD3)
/D4: J6.10, U4.16 (D4), U5.29 (SD4)
/D5: J6.8, U4.17 (D5), U5.30 (SD5)
/D6: J6.6, U4.18 (D6), U5.31 (SD6)
/D7: J6.4, U4.19 (D7), U5.32 (SD7)
/D8: J5.23, U5.110 (SD8)
/D9: J5.25, U5.109 (SD9)
/D10: J5.27, U5.108 (SD10)
/D11: J5.29, U5.107 (SD11)
/D12: J5.31, U5.106 (SD12)
/D13: J5.33, U5.105 (SD13)
/D14: J5.35, U5.104 (SD14)
/D15: J5.37, U5.103 (SD15)
/DACK0: J5.18, U4.68 (~DACKBA)
/DACK1: J6.33, U4.66 (~DACKBB)
/DACK3: J6.29, U4.64 (~DACKBC)
/DACK5: J5.22, U4.62 (~DACKBD)
/DRQ0: J5.20, U4.67 (DRQA)
/DRQ1: J6.35, U4.65 (DRQB)
/DRQ3: J6.31, U4.63 (DRQC)
/DRQ5: J5.24, U4.61 (DRQD)
/G: FB2.1, R4.1, U5.3 (G)
/HSYNC: FB5.1, U5.48 (HSYNC)
/IOCHRDY: J6.20, U5.157 (IOCHRDY)
/IRQ5: J6.45, U4.73 (IRQB)
/IRQ7: J6.41, U4.72 (IRQC)
/IRQ9: J6.7, U4.74 (IRQA)
/IRQ10: J5.8, U4.71 (IRQD)
/IRQ11: J5.10, U4.70 (IRQE)
/LA17: J5.17, U5.113 (SA17(LA17))
/LA18: J5.15, U5.114 (SA18(LA18))
/LA19: J5.13, U5.115 (SA19(LA19))
/LA20: J5.11, U5.116 (LA20)
/LA21: J5.9, U5.117 (LA21)
/LA22: J5.7, U5.118 (LA22)
/LA23: J5.5, U5.119 (LA23)
/LINE_L: J1.T, L2.2
/LINE_R: J1.R1, L3.2
/MAA0: U5.52 (MAA0), U11.6 (A0), U12.6 (A0)
/MAA1: U5.53 (MAA1), U11.7 (A1), U12.7 (A1)
/MAA2: U5.54 (MAA2), U11.8 (A2), U12.8 (A2)
/MAA3: U5.55 (MAA3), U11.9 (A3), U12.9 (A3)
/MAA4: U5.56 (MAA4), U11.11 (A4), U12.11 (A4)
/MAA5: U5.57 (MAA5), U11.12 (A5), U12.12 (A5)
/MAA6: U5.59 (MAA6), U11.13 (A6), U12.13 (A6)
/MAA7: U5.60 (MAA7), U11.14 (A7), U12.14 (A7)
/MAA8: U5.61 (MAA8), U11.15 (A8), U12.15 (A8)
/MAB0: U5.73 (MAB0), U13.6 (A0), U14.6 (A0)
/MAB1: U5.74 (MAB1), U13.7 (A1), U14.7 (A1)
/MAB2: U5.75 (MAB2), U13.8 (A2), U14.8 (A2)
/MAB3: U5.76 (MAB3), U13.9 (A3), U14.9 (A3)
/MAB4: U5.77 (MAB4), U13.11 (A4), U14.11 (A4)
/MAB5: U5.78 (MAB5), U13.12 (A5), U14.12 (A5)
/MAB6: U5.82 (MAB6), U13.13 (A6), U14.13 (A6)
/MAB7: U5.83 (MAB7), U13.14 (A7), U14.14 (A7)
/MAB8: U5.84 (MAB8), U13.15 (A8), U14.15 (A8)
/MD0: U5.64 (MD0), U11.1 (DQ1)
/MD1: U5.65 (MD1), U11.2 (DQ2)
/MD2: SW1.2, U5.66 (MD2), U11.18 (DQ3)
/MD3: R22.2, U5.67 (MD3), U11.19 (DQ4)
/MD4: U5.68 (MD4), U12.1 (DQ1)
/MD5: U5.70 (MD5), U12.2 (DQ2)
/MD6: U5.71 (MD6), U12.18 (DQ3)
/MD7: R24.2, U5.72 (MD7), U12.19 (DQ4)
/MD16: U5.89 (MD16), U13.1 (DQ1)
/MD17: U5.90 (MD17), U13.2 (DQ2)
/MD18: U5.91 (MD18), U13.18 (DQ3)
/MD19: U5.92 (MD19), U13.19 (DQ4)
/MD20: U5.93 (MD20), U14.1 (DQ1)
/MD21: U5.94 (MD21), U14.2 (DQ2)
/MD22: U5.95 (MD22), U14.18 (DQ3)
/MD23: U5.96 (MD23), U14.19 (DQ4)
/MIDI_L: C3.2, U6.1 (AOUTL)
/MIDI_R: C4.2, U6.2 (AOUTR)
/MSO: U4.58 (MSO), U6.16 (MIDI_IN)
/Monitor: FB4.1, R8.2, U5.46 (MONITOR)
/OSC: J6.59, R31.2, R32.2
/R: FB1.1, R3.1, U5.4 (R)
/RESET: C41.2, R36.2, U4.81 (RESET), U5.5 (RESET)
/RMD0: U5.43 (RMD0), U7.13 (O0)
/RMD1: SW1.1, U5.39 (RMD1), U7.14 (O1)
/RMD2: U5.38 (RMD2), U7.15 (O2)
/RMD3: U5.37 (RMD3), U7.18 (O3)
/RMD4: R25.2, U5.36 (RMD4), U7.19 (O4)
/RMD5: R37.2, U5.35 (RMD5), U7.20 (O5)
/RMD6: R23.2, U5.34 (RMD6), U7.21 (O6)
/RMD7: U5.33 (RMD7), U7.22 (O7)
/ROMBA0: U5.97 (ROMBA0), U7.31 (A14)
/SPKR: J3.16, L1.2
/VGA_B: C9.1, FB3.2, J3.13
/VGA_G: C8.1, FB2.2, J3.9
/VGA_HS: C23.1, FB5.2, J3.10
/VGA_MON: C24.1, FB4.2, J3.8
/VGA_R: C7.1, FB1.2, J3.5
/VGA_VS: C22.1, FB6.2, J3.14
/VSYNC: FB6.1, U5.47 (VSYNC)
/~CAS: C26.2, R17.2, U11.17 (~CAS), U12.17 (~CAS), U13.17 (~CAS), U14.17 (~CAS)
/~IOR: J6.27, U4.75 (~IORB), U5.153 (~IOR)
/~IOW: J6.25, R20.2, U4.76 (~IOWB)
/~MEMCS16: J5.4, R35.2, U5.102 (~MCS16)
/~MEMR: C29.1, J6.23, U5.155 (~MEMR)
/~MEMW: J6.21, U5.156 (~MEMW)
/~NMI: J6.2, U5.24 (~NMI)
/~RAS: C27.2, R18.2, U11.4 (~RAS), U12.4 (~RAS), U13.4 (~RAS), U14.4 (~RAS)
/~REFRESH: J6.37, U5.158 (ENMEM)
/~ROMCS: U5.45 (~ROMCS), U7.25 (~OE/VPP)
/~RSTB: U4.90 (~RSTB), U6.38 (~RST/~PD)
/~SBHE: J5.3, U5.99 (SBHE)
/~WE0: U5.88 (~WE0), U11.3 (~WE), U12.3 (~WE)
/~WE2: U5.87 (~WE2), U13.3 (~WE), U14.3 (~WE)
GND: C2.1, C7.2, C8.2, C9.2, C10.2, C11.2, C12.1, C13.1, C14.2, C17.2, C19.2, C22.2, C23.2, C24.2, C26.1, C27.1, C28.2, C29.2, C30.1, C31.1, C32.1, C33.1, C34.1, C35.1, C36.1, C38.2, C39.2, C40.2, C41.1, C42.2, C43.2, C44.1, C45.2, C46.1, C47.1, C48.1, C49.2, C50.2, C51.2, C52.2, C53.2, C55.2, C56.2, C57.2, C58.2, C59.2, C60.2, C61.2, C62.2, C63.2, C64.2, C65.2, C66.2, C67.2, C68.2, C69.2, C70.2, C71.2, C72.2, C73.2, C74.2, J1.R2, J1.S, J2.1, J2.3, J2.5, J3.3, J3.4, J3.7, J3.11, J3.12, J5.1, J5.2, J5.38, J5.40, J6.1, J6.61, J6.63, J6.64, R2.2, R3.2, R4.2, R5.2, R7.1, R14.2, R15.2, R19.1, R21.1, R22.1, R23.1, R24.1, R25.1, R30.2, R33.2, R34.2, R37.1, U1.1 (GND), U2.4 (V-), U3.8 (GND), U4.7 (GND), U4.24 (GND), U4.25 (PSEL1), U4.41 (GNDA), U4.52 (GND), U4.60 (GND), U4.77 (GND), U5.1 (AVSS2), U5.7 (DVSS2), U5.23 (VSS), U5.41 (VSS), U5.42 (VSS), U5.49 (EVIDEO), U5.50 (ECLK), U5.58 (VSS), U5.79 (VSS), U5.80 (VSS), U5.101 (VSS), U5.121 (VSS), U5.122 (VSS), U5.126 (AVSS), U5.128 (DVSS1), U5.143 (VSS), U5.160 (VSS), U6.4 (AGND), U6.7 (MICIN), U6.9 (GND), U6.10 (A0), U6.13 (GND)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
unnamed: C1.1, U4.37 (AUXA_L), U4.38 (AUXA_R)
unnamed: C1.2, C2.2, R1.2, R2.1
unnamed: C3.1, U4.35 (AUXB_L)
unnamed: C4.1, U4.36 (AUXB_R)
unnamed: C5.1, U4.48 (LINE_L)
unnamed: C5.2, L2.1
unnamed: C6.1, U4.49 (LINE_R)
unnamed: C6.2, L3.1
unnamed: C10.1, C11.1, U4.39 (CMR)
unnamed: C12.2, C13.2, R6.1, R7.2, U2.3 (+), U2.5 (+)
unnamed: C14.1, U4.42 (VREF)
unnamed: C15.1, R9.1, U2.1
unnamed: C15.2, L4.1
unnamed: C16.1, U4.45 (FOUT_L)
unnamed: C16.2, C17.1, U4.46 (CIN_L)
unnamed: C18.1, U4.44 (FOUT_R)
unnamed: C18.2, C19.1, U4.47 (CIN_R)
unnamed: C20.1, R10.1, R15.1
unnamed: C20.2, R11.2
unnamed: C21.1, R16.1, U2.7
unnamed: C21.2, L5.1
unnamed: C25.1, R12.1, R14.1
unnamed: C25.2, R13.2
unnamed: C28.1, R20.1, U5.154 (~IOW)
unnamed: C30.2, C31.2, U6.5 (VCM)
unnamed: C32.2, L6.1
unnamed: C33.2, C34.2, U6.34 (OUTVC12)
unnamed: C35.2, U6.40 (X2), Y2.1
unnamed: C36.2, U6.39 (X1), Y2.3
unnamed: C37.1, U5.125 (VLF)
unnamed: C40.1, L7.1, L8.1, R38.2, U1.2 (VO)
unnamed: J2.2, R26.1
unnamed: J2.4, R27.1
unnamed: J2.6, R29.1
unnamed: J4.3, J4.4
unnamed: J4.5, J4.6
unnamed: J4.7, J4.8
unnamed: J4.9, J4.10
unnamed: J6.3, R36.1
unnamed: JP1.2 (C), U5.21 (ALE)
unnamed: L1.1, R1.1
unnamed: L6.2, U5.131 (XTL1), Y1.1
unnamed: L9.1, R40.2, R41.2
unnamed: R10.2, U4.51 (AOUT_R)
unnamed: R9.2, R11.1, U2.2 (-)
unnamed: R12.2, U4.50 (AOUT_L)
unnamed: R13.1, R16.2, U2.6 (-)
unnamed: R17.1, U5.85 (~CAS)
unnamed: R18.1, U5.86 (~RAS)
unnamed: R19.2, SW1.4
unnamed: R21.2, SW1.3
unnamed: R26.2, U4.23 (MUTE/SECLK)
unnamed: R27.2, U4.22 (VOLUP/SEDI)
unnamed: R29.2, U4.21 (VOLDN/SEDO)
unnamed: R30.1, U4.20 (PSEL0/SECS)
unnamed: R31.1, U4.78 (XI)
unnamed: R32.1, U5.98 (ROMCLK)
unnamed: R33.1, U4.92 (GPIRQ)
unnamed: R34.1, U5.18 (IRSET)
unnamed: U3.15 (O0), U4.11 (AEN)
unnamed: U5.133 (XTL2), Y1.3
